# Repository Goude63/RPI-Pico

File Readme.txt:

December 24th, 2023:

Completed SigGen.py library.
Up to 6 signal generators can be instanciated, and will run using 0% CPU, 100% DMA.
Max tested output frequency: 4 MHz (fairly distorted).
Under 500 KHz output, very clean signal. Usage examples given at the end of dma.py and SigGen.py.
A low pass RC filter must be installed on output pins. Optionally also a decoupling capacitor to remove DC.

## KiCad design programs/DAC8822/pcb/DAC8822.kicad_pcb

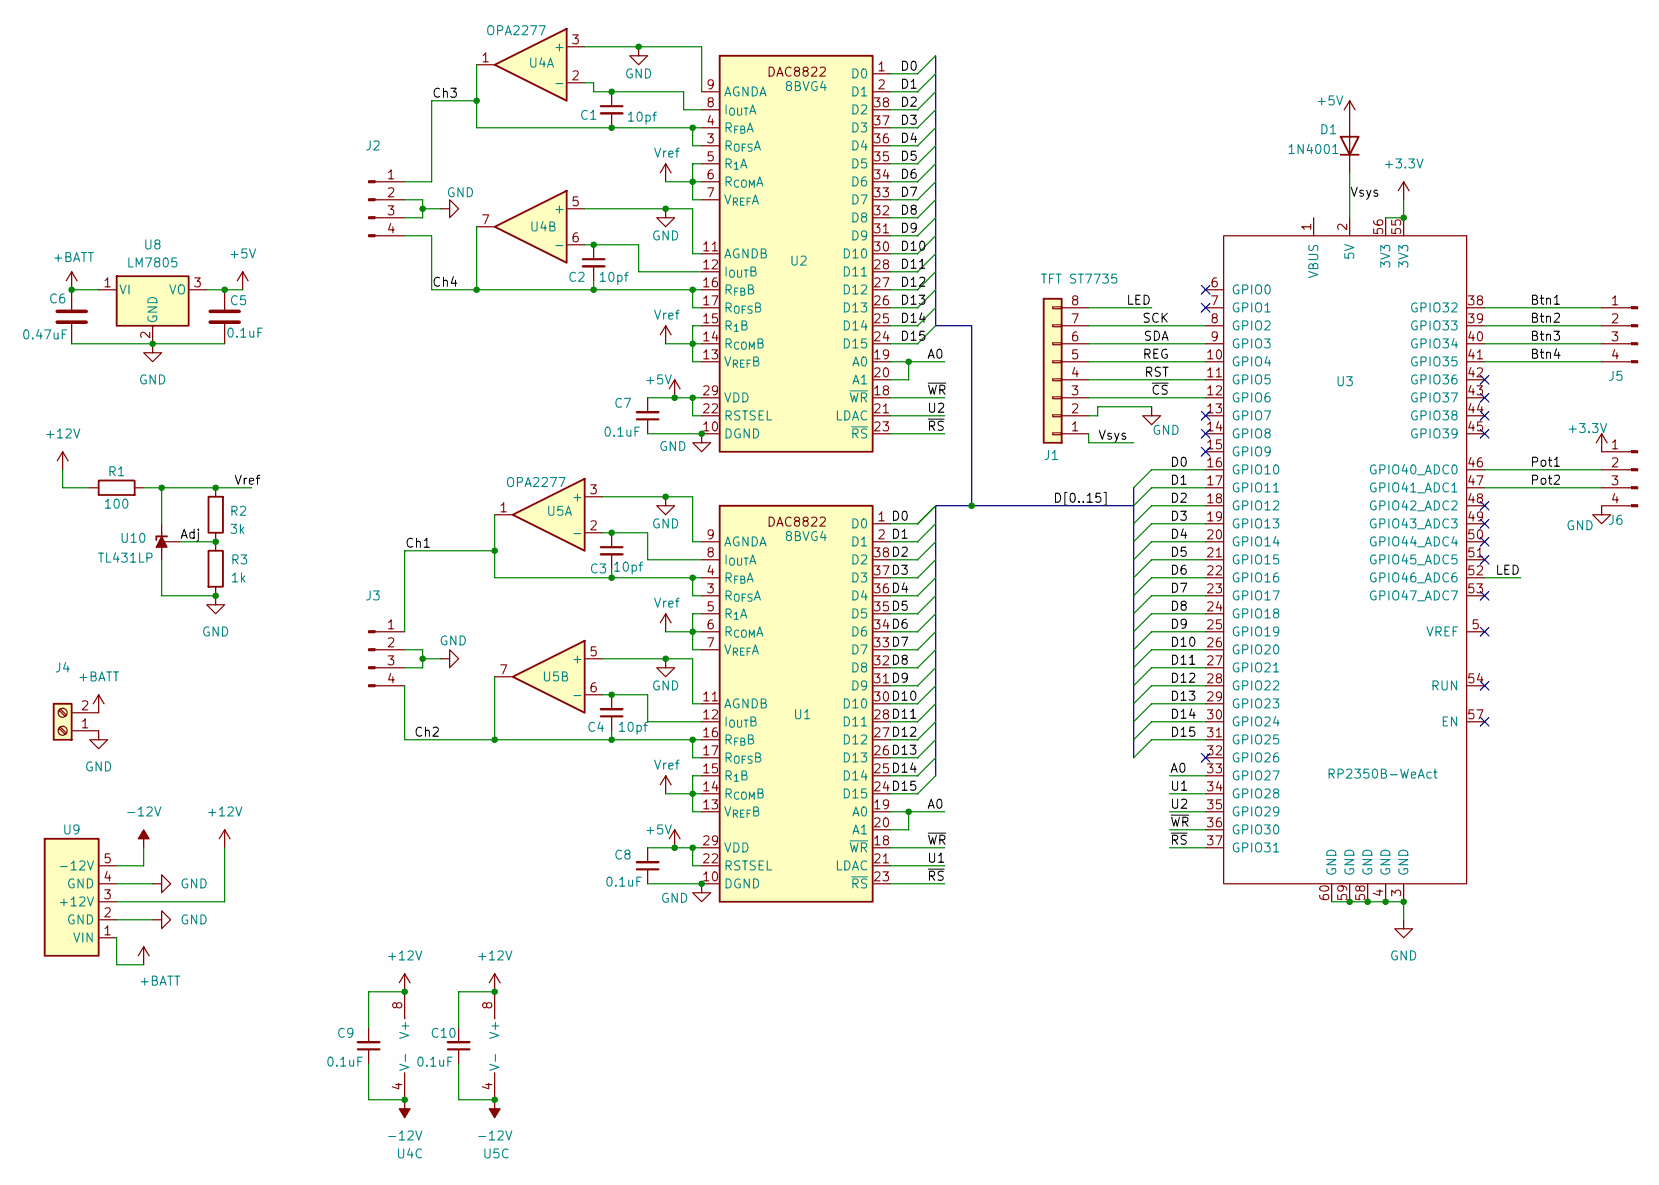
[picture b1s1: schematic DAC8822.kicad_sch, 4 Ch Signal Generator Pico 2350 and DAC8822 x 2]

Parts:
C1, C2, C3, C4: 10pf; C_0805_2012Metric
C5: 0.1uF; C_Disc_D5.0mm_W2.5mm_P2.50mm
C6: 0.47uF; C_Disc_D5.0mm_W2.5mm_P2.50mm
C7, C8, C9, C10: 0.1uF; C_0805_2012Metric
D1: 1N4001; D_DO-41_SOD81_P10.16mm_Horizontal
J1: TFT ST7735; ST7735
J2, J3, J5, J6: Conn_01x04_Pin; PinHeader_1x04_P1.27mm_Vertical
J4: Screw_Terminal_01x02; TerminalBlock_Xinya_XY308-2.54-2P_1x02_P2.54mm_Horizontal
R1: 100; R_0805_2012Metric
R2: 3k; R_0805_2012Metric
R3: 1k; R_0805_2012Metric
U1, U2: 8BVG4; TSSOP-38_4.4x9.7mm_P0.5mm
U3: RP2350B-WeAct; Rp2350b-WeAct
U4, U5: OPA2277; SOIC-8_3.9x4.9mm_P1.27mm
U8: LM7805; TO-220-3_Vertical
U9: +12-12PSU
U10: TL431LP; TO-92_Inline

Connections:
+3.3V: J6.1, U3.55 (3V3), U3.56 (3V3)
+5V: C5.2, C7.2, C8.2, D1.2 (A), U1.22 (RSTSEL), U1.29 (VDD), U2.22 (RSTSEL), U2.29 (VDD), U8.3 (VO)
+12V: C9.2, C10.2, R1.1, U4.8 (V+), U5.8 (V+), U9.3 (+12V)
+BATT: C6.1, J4.2, U8.1 (VI), U9.1 (VIN)
-12V: C9.1, C10.1, U4.4 (V-), U5.4 (V-), U9.5 (-12V)
/A0: U1.19 (A0), U1.20 (A1), U2.19 (A0), U2.20 (A1), U3.33 (GPIO27)
/Adj: R2.1, R3.1, U10.1 (REF)
/Btn1: J5.1, U3.38 (GPIO32)
/Btn2: J5.2, U3.39 (GPIO33)
/Btn3: J5.3, U3.40 (GPIO34)
/Btn4: J5.4, U3.41 (GPIO35)
/Ch1: C3.2, J3.1, U1.3 (R_{OFS}A), U1.4 (R_{FB}A), U5.1
/Ch2: C4.1, J3.4, U1.16 (R_{FB}B), U1.17 (R_{OFS}B), U5.7
/Ch3: C1.2, J2.1, U2.3 (R_{OFS}A), U2.4 (R_{FB}A), U4.1
/Ch4: C2.2, J2.4, U2.16 (R_{FB}B), U2.17 (R_{OFS}B), U4.7
/D0: U1.1 (D0), U2.1 (D0), U3.16 (GPIO10)
/D1: U1.2 (D1), U2.2 (D1), U3.17 (GPIO11)
/D2: U1.38 (D2), U2.38 (D2), U3.18 (GPIO12)
/D3: U1.37 (D3), U2.37 (D3), U3.19 (GPIO13)
/D4: U1.36 (D4), U2.36 (D4), U3.20 (GPIO14)
/D5: U1.35 (D5), U2.35 (D5), U3.21 (GPIO15)
/D6: U1.34 (D6), U2.34 (D6), U3.22 (GPIO16)
/D7: U1.33 (D7), U2.33 (D7), U3.23 (GPIO17)
/D8: U1.32 (D8), U2.32 (D8), U3.24 (GPIO18)
/D9: U1.31 (D9), U2.31 (D9), U3.25 (GPIO19)
/D10: U1.30 (D10), U2.30 (D10), U3.26 (GPIO20)
/D11: U1.28 (D11), U2.28 (D11), U3.27 (GPIO21)
/D12: U1.27 (D12), U2.27 (D12), U3.28 (GPIO22)
/D13: U1.26 (D13), U2.26 (D13), U3.29 (GPIO23)
/D14: U1.25 (D14), U2.25 (D14), U3.30 (GPIO24)
/D15: U1.24 (D15), U2.24 (D15), U3.31 (GPIO25)
/LED: J1.8, U3.52 (GPIO46_ADC6)
/Pot1: J6.2, U3.46 (GPIO40_ADC0)
/Pot2: J6.3, U3.47 (GPIO41_ADC1)
/REG: J1.5, U3.10 (GPIO4)
/RST: J1.4, U3.11 (GPIO5)
/SCK: J1.7, U3.8 (GPIO2)
/SDA: J1.6, U3.9 (GPIO3)
/U1: U1.21 (LDAC), U3.34 (GPIO28)
/U2: U2.21 (LDAC), U3.35 (GPIO29)
/Vsys: D1.1 (K), J1.1, U3.2 (5V)
/~CS: J1.3, U3.12 (GPIO6)
/~RS: U1.23 (~RS), U2.23 (~RS), U3.37 (GPIO31)
/~WR: U1.18 (~WR), U2.18 (~WR), U3.36 (GPIO30)
GND: C5.1, C6.2, C7.1, C8.1, J1.2, J2.2, J2.3, J3.2, J3.3, J4.1, J6.4, R3.2, U1.9 (AGNDA), U1.10 (DGND), U1.11 (AGNDB), U2.9 (AGNDA), U2.10 (DGND), U2.11 (AGNDB), U3.3 (GND), U3.4 (GND), U3.58 (GND), U3.59 (GND), U3.60 (GND), U4.3 (+), U4.5 (+), U5.3 (+), U5.5 (+), U8.2 (GND), U9.2 (GND), U9.4 (GND), U10.2 (A)
unnamed: C3.1, U1.8 (I_{OUT}A), U5.2 (-)
unnamed: C4.2, U1.12 (I_{OUT}B), U5.6 (-)
unnamed: C1.1, U2.8 (I_{OUT}A), U4.2 (-)
unnamed: C2.1, U2.12 (I_{OUT}B), U4.6 (-)
Vref: R1.2, R2.2, U1.5 (R_{1}A), U1.6 (R_{COM}A), U1.7 (V_{REF}A), U1.13 (V_{REF}B), U1.14 (R_{COM}B), U1.15 (R_{1}B), U2.5 (R_{1}A), U2.6 (R_{COM}A), U2.7 (V_{REF}A), U2.13 (V_{REF}B), U2.14 (R_{COM}B), U2.15 (R_{1}B), U10.3 (K)

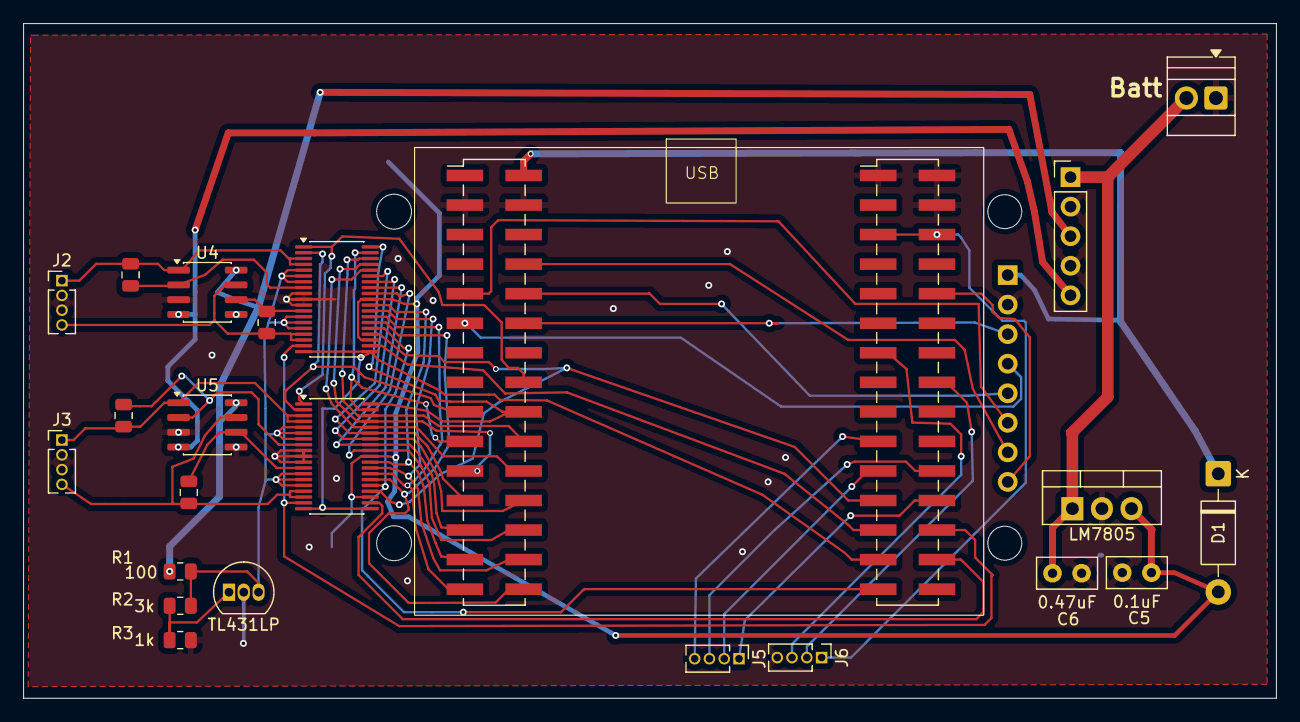
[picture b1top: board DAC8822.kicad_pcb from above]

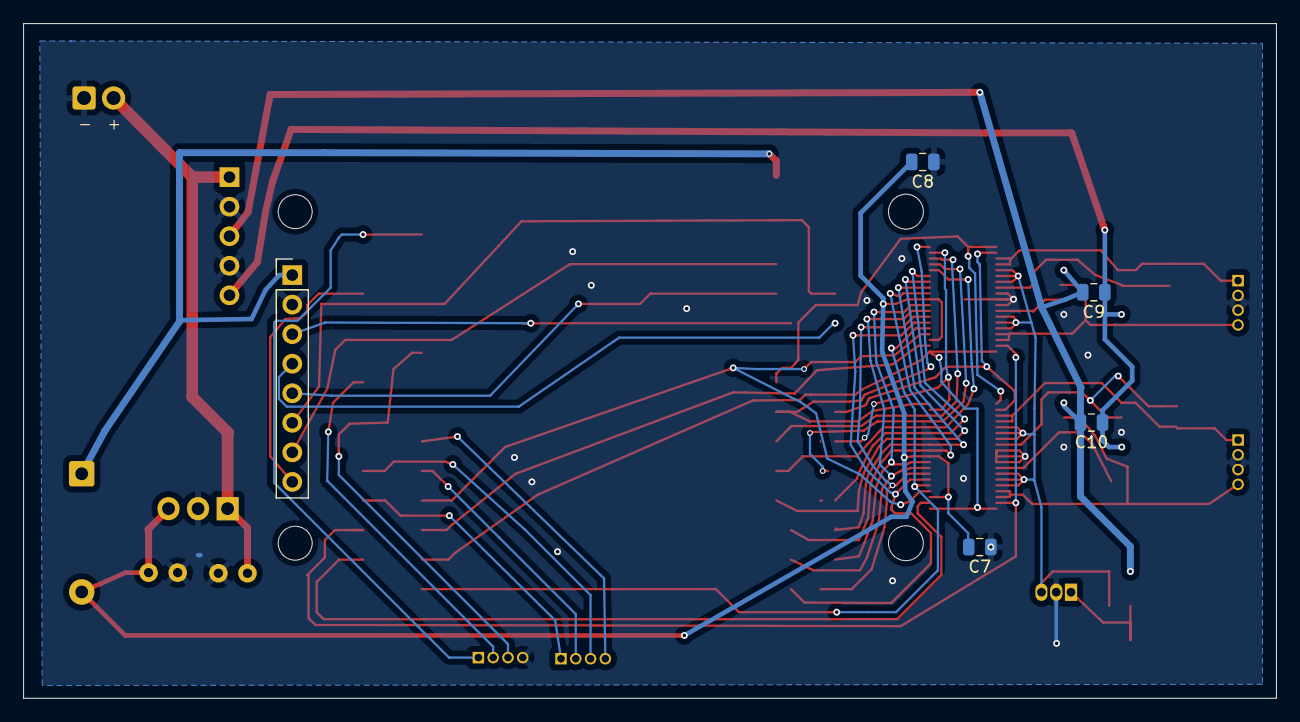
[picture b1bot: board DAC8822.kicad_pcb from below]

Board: 2 copper layers, 107.7 x 58.0 mm, 28 parts (5 on the bottom side), 50 nets.

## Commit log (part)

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2023-12-22 Include usage example
    Included test in lib (comment when tests are done)
    Modified SetChData() to make the call look better
    TBD: Not all tested, and fic bug on chain channel
2023-12-24 Add files via upload
    First mostly tested SigGen using dma.y.
2023-12-29 Add files via upload
    - Moved FREE_DMA list from SigGen to Dma module
    - Added Dma.DeInit() and __del__
    - Added "rnd" waveform
2024-01-01 Add files via upload
    Work in progress. Non DMA read functional
2024-01-02 Add files via upload
    Work in progress on adc, and minor changes to dma and SigGen
2024-01-04 Work in progress Adc using Dma
    Added Dma.Info to help debug current Dma channel status
2024-01-05 Add files via upload
    Work in progress Dma/Adc/PIO
    - ADC => DMA1 => PIO => DMA2 => ping pong buffers Working!
    - TBD: PIO generates IRQs when its time to use ping or pong,
    the IRQ routine needs to be written (calback to user code, or write to file...)
2024-01-05 Add files via upload
    First functional Adc => Dma => memory => binary file
    TBD: Test "CB" version where data is sent to user code through a callback function
2024-01-10 Add files via upload
    - Changed method for tracking used DMA channels. Now using EN bit instead of maintaining a list
    - SDCard.py: Now disabling DMA channels used by spi un UMount()
2024-01-11 Add files via upload
    Latest
2024-01-11 Add files via upload
    Microphone recorder using DMA, and SD card + Labview utility to plaback and convert to wave files
2024-01-11 mic_recorder.py typo on comment
2024-01-11 Add files via upload
    Navigation improvements
2024-01-14 Add files via upload
    Sync with my personal subversion files
    Minor cosmetic changes
2024-01-14 Add files via upload
    Improved interface and multi file auto chaining during playback
2024-01-14 Add files via upload
    - Fixed "out of memory error" by calling gc.collect() between files
    - Improved le UI interface response time. Long press = 2 sec instead of 3
2024-04-23 First commit
    Program using PWM to play keywords to alexa.
    - Using a transistor to drive speaker
    - Using CH9120 UART<->ethernet board to allow controling from network.
    - Goal: Allow various programs in mu LAN to request Alexa actions by actually saying sentenses to Alexa
    - Will work with other voice activated systems...
    TBD: Implement UART rx code. This incomplete version needs manualy typing request as shown in example at the end of Alexa.py file
2024-05-01 svn sync
2024-06-08 sync
2024-12-11 Option to use gpio as module's ground
    This is useful when soldering the bme280 module directly on the pico: no wires,
2025-09-08 Add files via upload
    Work in progress. Monitor and logs my car 12v battery (I have an issue with something in the car drawing too much and draining the battery)
    The project needs a voltage divisor to the Analog input zero (100k/10k) to make sure pico input is under 3.3v
    Using deep sleep: 6ma for 5 min, and 18ma for 1-2 sec when reading/logging. I only log if voltage changes more than 0.05V
    I have a wifi access near my car so the final version will log the data on a raspberry pi 4 server.
    T
2026-01-28 V0.98
    Added Auto-Scale and sync totals with lv gui
2026-01-28 V 0.98
    Added Auto-Scale and sync totals with lv gui
2026-03-18 Add ReadMe for ST7735 driver modifications
    Document modifications made to the ST7735 driver, including support for larger font heights, PWM brightness control, and removal of character size multiplication.
2026-03-21 Working on GUI
    Mostly completed knobs functions to edit numbers
2026-03-24 Revise ReadMe.txt with driver modifications
    Updated the ReadMe.txt to reflect various modifications made to the ST7735 driver, including support for larger fonts, PWM brightness control, and changes to character rendering.
2026-03-24 Fairly completed UI
